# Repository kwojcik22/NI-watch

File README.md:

# NI-watch

NI-watch is an embedded watch project based on the STM32F0 MCU family. The firmware is designed for a custom hardware platform with RTC support, button input, LED feedback, alarm management, and UART-based debug logging.

## Post-production Images

  Top and bottom photos exported from the post-production media folder:

## Project Structure

A compact overview of the main repository layout:

```text
NI-watch/
├── hardware/
│   ├── doc/
│   └── zegarek/
│       ├── fp-lib-table
│       ├── jlcpcb/
│       │   └── production_files/
│       ├── Library.pretty/
│       ├── MCU.kicad_sch
│       ├── NIXIE.kicad_sch
│       ├── PWR_MNG.kicad_sch
│       ├── zegarek.kicad_pcb
│       ├── zegarek.kicad_prl
│       ├── zegarek.kicad_pro
│       ├── zegarek.kicad_sch
├── README.md
└── software/
    └── TheWatch/
        ├── Core/
        │   ├── Inc/
        │   │   ├── bsp/
        │   │   ├── logger/
        │   │   └── Manager/
        │   └── Src/
        ├── Debug/
        ├── Drivers/
        ├── STM32F091RCTX_FLASH.ld
        ├── TheWatch Debug.launch
        └── TheWatch.ioc
```

The main firmware path is `software/TheWatch/Core/`, where the primary application, peripheral drivers, and helpers are located.

## Hardware Status

The `hardware/` folder contains the KiCad board project and the JLCPCB manufacturing export data for the watch design.

- `hardware/zegarek/zegarek.kicad_pcb` is the PCB layout file.
- The project includes additional schematic sheets for the MCU and power sections: `MCU.kicad_sch`, `NIXIE.kicad_sch`, and `PWR_MNG.kicad_sch`.
- `hardware/zegarek/Library.pretty/` contains custom local footprint libraries used by the design.
- `hardware/zegarek/jlcpcb/` contains fabrication outputs and assembly data exported for JLCPCB.
  - `hardware/zegarek/jlcpcb/production_files/gerber.zip` contains the generated Gerber files for board manufacturing.
  - `hardware/zegarek/jlcpcb/production_files/` contains the exported BOM and CPL files for assembly.

## MCU Peripherals

The table below lists only the MCU peripherals used by the firmware and their primary roles.

| Peripheral | Usage | Pins / Notes |
|---|---|---|
| RTC | Timekeeping, Alarm A | on-chip RTC |
| GPIO (Buttons) | User input (short/long press) | USER: `GPIOA/B` |
| LEDs | debug feedback & heartbeat | `GPIO_LED0/1/2` |
| UART | Debug logging (logger) | USART (see `usart.c`) |
| Timers | Heartbeat, alarm buzzer and non-blocking timers | TIMx (system timers) |

## Features

- 24-hour RTC operation using the on-chip RTC peripheral
- Alarm support using RTC Alarm A
- Button press detection with short press and long press events
- LED toggling for user feedback and heartbeat status
- UART logging for debug and runtime information

## User Interaction

### Buttons

- Blue button (configured on GPIOC pin 13)
  - Short press: read current RTC time and print it to the logger
  - Long press: set the RTC alarm to one minute ahead of the current time and log the alarm value
- Additional buttons on GPIOA and GPIOB toggle onboard LEDs for quick manual feedback

### LEDs

- LEDs connected to `GPIO_LED0`, `GPIO_LED1`, and `GPIO_LED2` toggle when their respective buttons are pressed
- `LD2` is toggled periodically by a non-blocking timer to provide a simple heartbeat indicator

## RTC and Alarm Behavior

- RTC is initialized with default time and date values
- Alarm A is enabled at startup and can be updated by user input
- Alarm behavior and interrupt handling are logged through the UART debug logger

## Debugging and Logging

- Logging is implemented through `logger/logger.h` and `logger/logger.c`
- Log levels include `INFO`, `WARN`, `ERROR`, and `DEBUG`
- The firmware prints time reads, alarm configuration, button events, and interrupt notices

## Build Notes

- The firmware is built using STM32Cube-generated HAL code and project files
- The target MCU is an STM32F091RCTX device
- `software/TheWatch/STM32F091RCTX_FLASH.ld` contains the linker script for flash layout

## Notes

This README describes the current firmware behavior as implemented in the provided source files. The project is a work in progress and can be extended with additional watch features such as display output, time setting via buttons

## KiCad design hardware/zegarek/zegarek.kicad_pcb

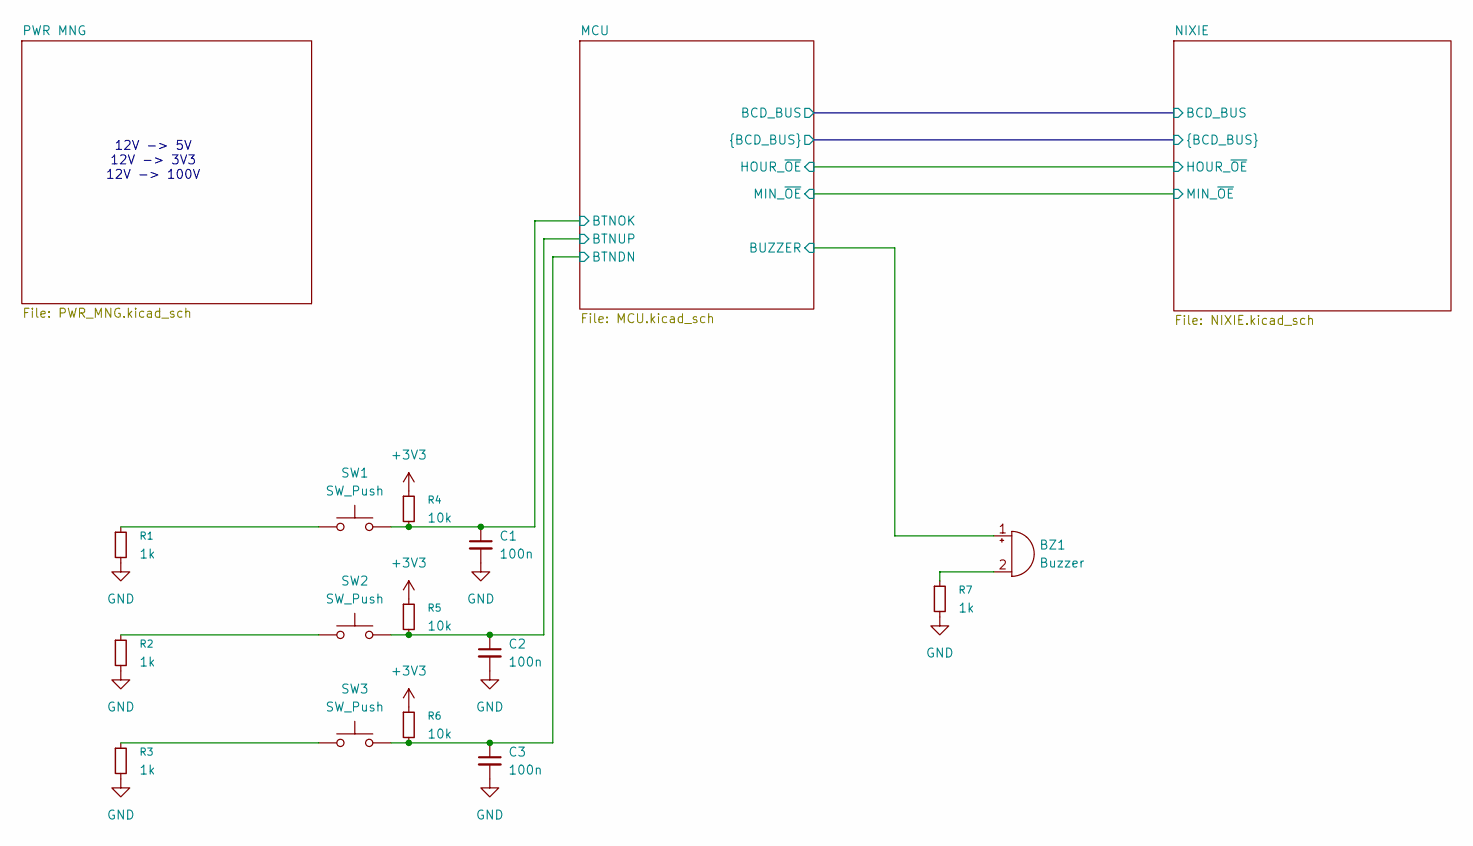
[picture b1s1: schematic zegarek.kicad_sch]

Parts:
BZ1: Buzzer; MagneticBuzzer_StarMicronics_HMB
C1, C2, C3: 100n; C_1206_3216Metric_Pad1.33x1.80mm_HandSolder; LCSC C152824
R1, R3, R7: 1k; R_0603_1608Metric_Pad0.98x0.95mm_HandSolder; LCSC C2074140
R2: 1k; R_0603_1608Metric_Pad0.98x0.95mm_HandSolder
R4, R5, R6: 10k; R_0603_1608Metric_Pad0.98x0.95mm_HandSolder; LCSC C3152147
SW1, SW2, SW3: SW_Push; SW_Push_1P1T_NO_CK_KMR2

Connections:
+3V3: R4.1, R5.1, R6.1; also elsewhere on the board
/MCU/BTNDN: C3.1, R6.2, SW3.2; also elsewhere on the board
/MCU/BTNOK: C1.1, R4.2, SW1.2; also elsewhere on the board
/MCU/BTNUP: C2.1, R5.2, SW2.2; also elsewhere on the board
/MCU/BUZZER: BZ1.1 (+); also elsewhere on the board
GND: C1.2, C2.2, C3.2, R1.2, R2.2, R3.2, R7.2; also elsewhere on the board
unnamed: BZ1.2 (-), R7.1
unnamed: R1.1, SW1.1
unnamed: R2.1, SW2.1
unnamed: R3.1, SW3.1

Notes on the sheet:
12V -> 5V 12V -> 3V3 12V -> 100V

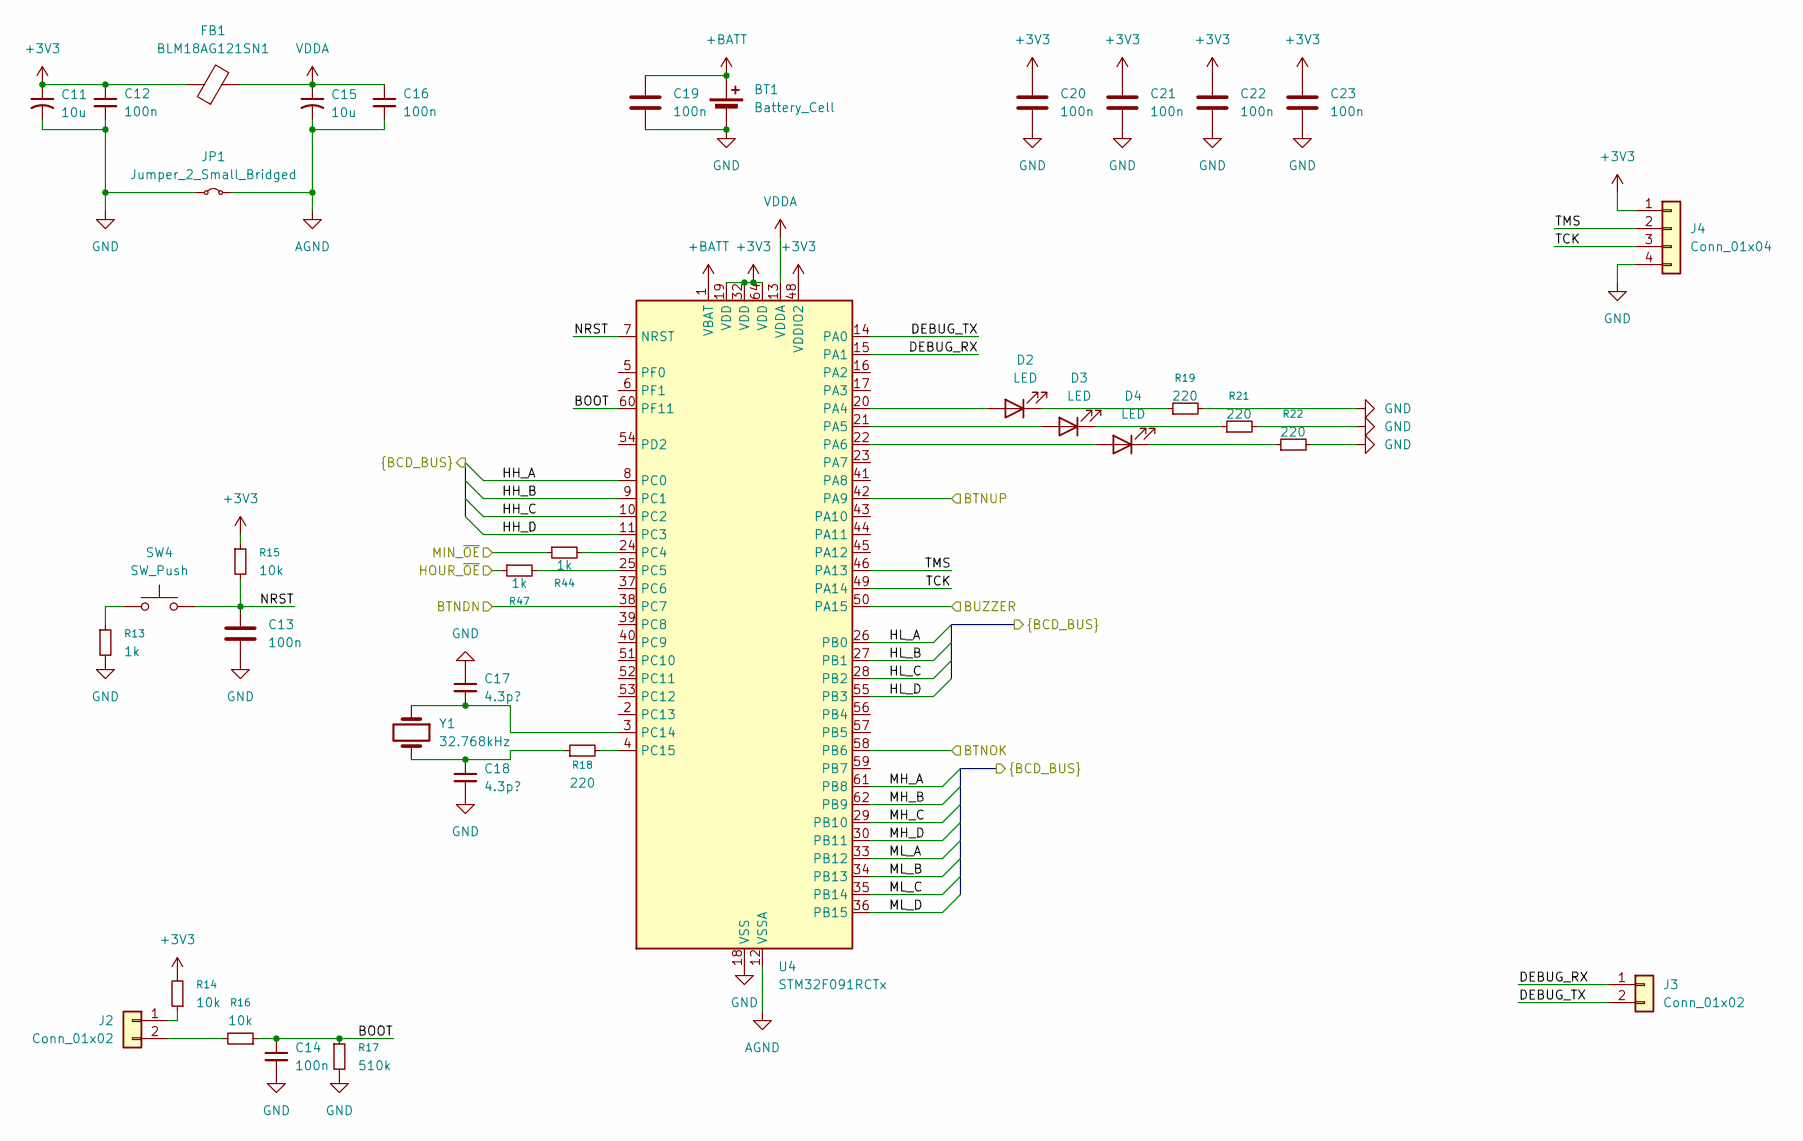
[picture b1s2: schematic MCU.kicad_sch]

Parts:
BT1: Battery_Cell; BatteryHolder_MYOUNG_BS-07-A1BJ001_CR2032; LCSC C964750
C11, C15: 10u; C_1206_3216Metric_Pad1.33x1.80mm_HandSolder; LCSC C49326738
C12, C14, C16, C19, C20, C21, C22, C23: 100n; C_1206_3216Metric_Pad1.33x1.80mm_HandSolder; LCSC C152824
C13: 100n; C_0603_1608Metric_Pad1.08x0.95mm_HandSolder; LCSC C1590
C17, C18: 4.3p?; C_0603_1608Metric_Pad1.08x0.95mm_HandSolder; LCSC C424850
D2: LED; LED_0603_1608Metric_Pad1.05x0.95mm_HandSolder; LCSC C89811
D3: LED; LED_0603_1608Metric_Pad1.05x0.95mm_HandSolder; LCSC C2286
D4: LED; LED_0603_1608Metric_Pad1.05x0.95mm_HandSolder; LCSC C2288
FB1: BLM18AG121SN1; L_0603_1608Metric_Pad1.05x0.95mm_HandSolder; LCSC C76892
J2, J3: Conn_01x02; PinHeader_1x02_P2.54mm_Vertical; LCSC C86471
J4: Conn_01x04; PinHeader_1x04_P2.54mm_Vertical; LCSC C124378
JP1: Jumper_2_Small_Bridged; SolderJumper-2_P1.3mm_Bridged_RoundedPad1.0x1.5mm
R13: 1k; R_0603_1608Metric_Pad0.98x0.95mm_HandSolder; LCSC C2074140
R14, R16: 10k; R_0603_1608Metric_Pad0.98x0.95mm_HandSolder; LCSC C15401
R15: 10k; R_0603_1608Metric_Pad0.98x0.95mm_HandSolder; LCSC C3152147
R17: 510k; R_0603_1608Metric_Pad0.98x0.95mm_HandSolder; LCSC C23192
R18, R19, R21, R22: 220; R_0603_1608Metric_Pad0.98x0.95mm_HandSolder; LCSC C54920883
R44, R47: 1k; R_0603_1608Metric_Pad0.98x0.95mm_HandSolder
SW4: SW_Push; SW_Push_1P1T_NO_CK_KMR2
U4: STM32F091RCTx; LQFP-64_10x10mm_P0.5mm; LCSC C89056
Y1: 32.768kHz; Crystal_AT310_D3.0mm_L10.0mm_Horizontal; LCSC C2236

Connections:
+3V3: C11.1, C12.1, C20.1, C21.1, C22.1, C23.1, FB1.1, J4.1, R14.2, R15.1, U4.19 (VDD), U4.32 (VDD), U4.48 (VDDIO2), U4.64 (VDD); also elsewhere on the board
+BATT: BT1.1 (+), C19.1, U4.1 (VBAT)
/MCU/BOOT: C14.1, R16.1, R17.1, U4.60 (PF11)
/MCU/BTNDN: U4.38 (PC7); also elsewhere on the board
/MCU/BTNOK: U4.58 (PB6); also elsewhere on the board
/MCU/BTNUP: U4.42 (PA9); also elsewhere on the board
/MCU/BUZZER: U4.50 (PA15); also elsewhere on the board
/MCU/DEBUG_RX: J3.1, U4.15 (PA1)
/MCU/DEBUG_TX: J3.2, U4.14 (PA0)
/MCU/HH_A: U4.8 (PC0); also elsewhere on the board
/MCU/HH_B: U4.9 (PC1); also elsewhere on the board
/MCU/HH_C: U4.10 (PC2); also elsewhere on the board
/MCU/HH_D: U4.11 (PC3); also elsewhere on the board
/MCU/HL_A: U4.26 (PB0); also elsewhere on the board
/MCU/HL_B: U4.27 (PB1); also elsewhere on the board
/MCU/HL_C: U4.28 (PB2); also elsewhere on the board
/MCU/HL_D: U4.55 (PB3); also elsewhere on the board
/MCU/HOUR_~OE: R47.1; also elsewhere on the board
/MCU/MH_A: U4.61 (PB8); also elsewhere on the board
/MCU/MH_B: U4.62 (PB9); also elsewhere on the board
/MCU/MH_C: U4.29 (PB10); also elsewhere on the board
/MCU/MH_D: U4.30 (PB11); also elsewhere on the board
/MCU/MIN_~OE: R44.1; also elsewhere on the board
/MCU/ML_A: U4.33 (PB12); also elsewhere on the board
/MCU/ML_B: U4.34 (PB13); also elsewhere on the board
/MCU/ML_C: U4.35 (PB14); also elsewhere on the board
/MCU/ML_D: U4.36 (PB15); also elsewhere on the board
/MCU/NRST: C13.1, R15.2, SW4.2, U4.7 (NRST)
/MCU/TCK: J4.3, U4.49 (PA14)
/MCU/TMS: J4.2, U4.46 (PA13)
AGND: C15.2, C16.2, JP1.2 (B), U4.12 (VSSA)
GND: BT1.2 (-), C11.2, C12.2, C13.2, C14.2, C17.1, C18.2, C19.2, C20.2, C21.2, C22.2, C23.2, J4.4, JP1.1 (A), R13.2, R17.2, R19.2, R21.2, R22.2, U4.18 (VSS), U4.31 (VSS), U4.47 (VSS), U4.63 (VSS); also elsewhere on the board
unnamed: C18.1, R18.1, Y1.2
unnamed: D2.2 (A), U4.20 (PA4)
unnamed: D2.1 (K), R19.1
unnamed: D3.2 (A), U4.21 (PA5)
unnamed: D3.1 (K), R21.1
unnamed: D4.2 (A), U4.22 (PA6)
unnamed: D4.1 (K), R22.1
unnamed: J2.1, R14.1
unnamed: J2.2, R16.2
unnamed: R13.1, SW4.1
unnamed: R44.2, U4.24 (PC4)
unnamed: R47.2, U4.25 (PC5)
unnamed: C17.2, U4.3 (PC14), Y1.1
unnamed: R18.2, U4.4 (PC15)
VDDA: C15.1, C16.1, FB1.2, U4.13 (VDDA)

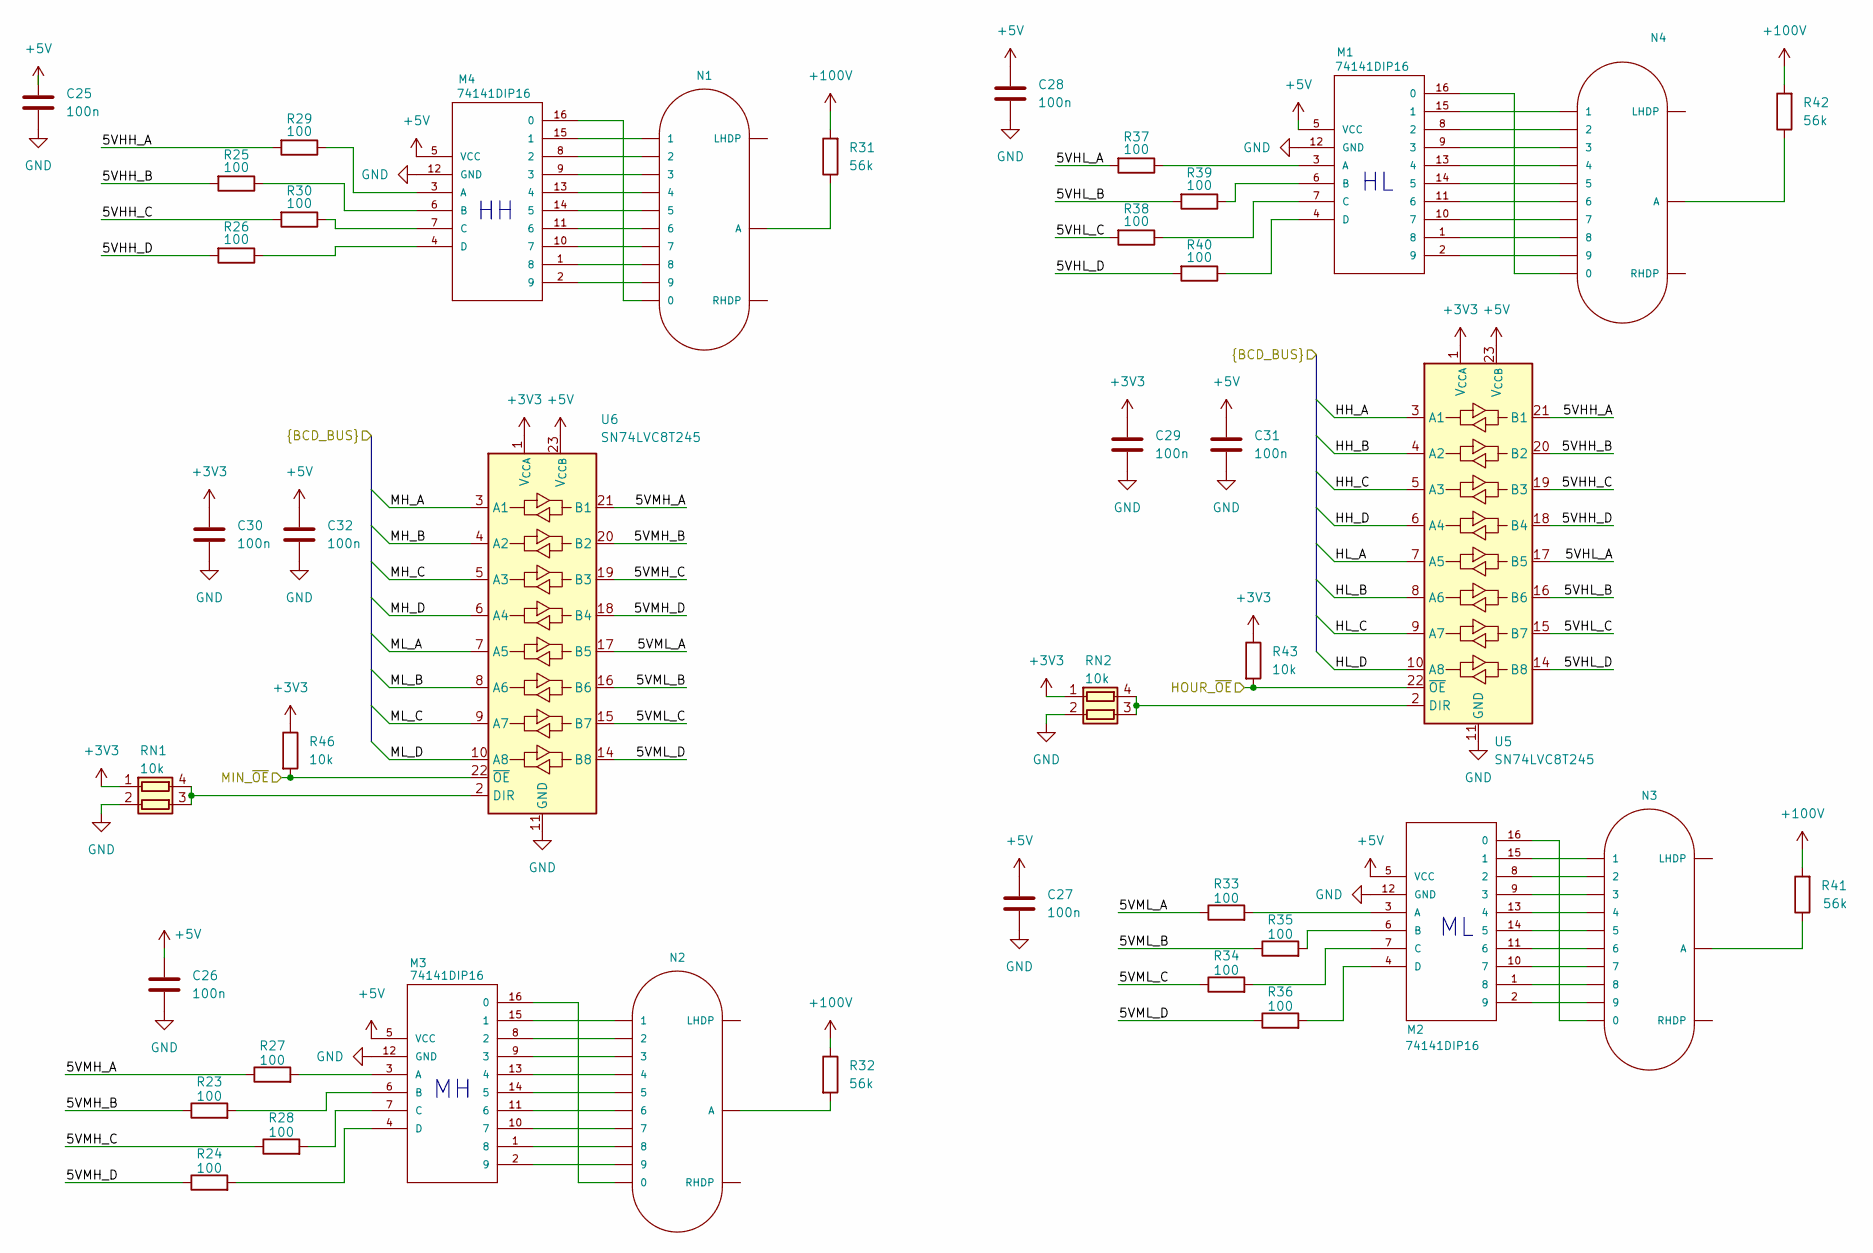
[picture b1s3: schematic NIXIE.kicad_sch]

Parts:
C25, C26, C27, C28, C29, C30, C31, C32: 100n; C_1206_3216Metric_Pad1.33x1.80mm_HandSolder; LCSC C152824
M1, M2, M3, M4: 74141DIP16; nixiemisc-DIP16
N1, N2, N3, N4: IN-14; nixies-us-IN-14
R23, R24, R25, R26, R27, R28, R29, R30, R33, R34, R35, R36, R37, R38, R39: 100; R_0603_1608Metric_Pad0.98x0.95mm_HandSolder; LCSC C3152153
R31, R32, R41, R42: 56k; R_1206_3216Metric_Pad1.30x1.75mm_HandSolder; LCSC C22809
R40: 100; R_0603_1608Metric_Pad0.98x0.95mm_HandSolder; LCSC C17901
R43, R46: 10k; R_0603_1608Metric_Pad0.98x0.95mm_HandSolder
RN1, RN2: 10k; R_Array_Convex_2x0606
U5, U6: SN74LVC8T245; TSSOP-24_4.4x7.8mm_P0.65mm

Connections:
+3V3: C29.1, C30.1, R43.1, R46.1, RN1.1 (R1.1), RN2.1 (R1.1), U5.1 (V_{CCA}), U6.1 (V_{CCA}); also elsewhere on the board
+5V: C25.1, C26.1, C27.1, C28.1, C31.1, C32.1, M1.5 (VCC), M2.5 (VCC), M3.5 (VCC), M4.5 (VCC), U5.23 (V_{CCB}), U5.24 (V_{CCB}), U6.23 (V_{CCB}), U6.24 (V_{CCB}); also elsewhere on the board
+100V: R31.2, R32.1, R41.2, R42.2; also elsewhere on the board
/MCU/HH_A: U5.3 (A1); also elsewhere on the board
/MCU/HH_B: U5.4 (A2); also elsewhere on the board
/MCU/HH_C: U5.5 (A3); also elsewhere on the board
/MCU/HH_D: U5.6 (A4); also elsewhere on the board
/MCU/HL_A: U5.7 (A5); also elsewhere on the board
/MCU/HL_B: U5.8 (A6); also elsewhere on the board
/MCU/HL_C: U5.9 (A7); also elsewhere on the board
/MCU/HL_D: U5.10 (A8); also elsewhere on the board
/MCU/HOUR_~OE: R43.2, U5.22 (~OE); also elsewhere on the board
/MCU/MH_A: U6.3 (A1); also elsewhere on the board
/MCU/MH_B: U6.4 (A2); also elsewhere on the board
/MCU/MH_C: U6.5 (A3); also elsewhere on the board
/MCU/MH_D: U6.6 (A4); also elsewhere on the board
/MCU/MIN_~OE: R46.2, U6.22 (~OE); also elsewhere on the board
/MCU/ML_A: U6.7 (A5); also elsewhere on the board
/MCU/ML_B: U6.8 (A6); also elsewhere on the board
/MCU/ML_C: U6.9 (A7); also elsewhere on the board
/MCU/ML_D: U6.10 (A8); also elsewhere on the board
/NIXIE/5VHH_A: R29.2, U5.21 (B1)
/NIXIE/5VHH_B: R25.2, U5.20 (B2)
/NIXIE/5VHH_C: R30.2, U5.19 (B3)
/NIXIE/5VHH_D: R26.2, U5.18 (B4)
/NIXIE/5VHL_A: R37.2, U5.17 (B5)
/NIXIE/5VHL_B: R39.2, U5.16 (B6)
/NIXIE/5VHL_C: R38.2, U5.15 (B7)
/NIXIE/5VHL_D: R40.2, U5.14 (B8)
/NIXIE/5VMH_A: R27.1, U6.21 (B1)
/NIXIE/5VMH_B: R23.1, U6.20 (B2)
/NIXIE/5VMH_C: R28.1, U6.19 (B3)
/NIXIE/5VMH_D: R24.1, U6.18 (B4)
/NIXIE/5VML_A: R33.1, U6.17 (B5)
/NIXIE/5VML_B: R35.1, U6.16 (B6)
/NIXIE/5VML_C: R34.1, U6.15 (B7)
/NIXIE/5VML_D: R36.1, U6.14 (B8)
GND: C25.2, C26.2, C27.2, C28.2, C29.2, C30.2, C31.2, C32.2, M1.12 (GND), M2.12 (GND), M3.12 (GND), M4.12 (GND), RN1.2 (R2.1), RN2.2 (R2.1), U5.11 (GND), U5.12 (GND), U5.13 (GND), U6.11 (GND), U6.12 (GND), U6.13 (GND); also elsewhere on the board
unnamed: M1.16 (0), N4.0
unnamed: M1.15 (1), N4.1
unnamed: M1.8 (2), N4.2
unnamed: M1.9 (3), N4.3
unnamed: M1.13 (4), N4.4
unnamed: M1.14 (5), N4.5
unnamed: M1.11 (6), N4.6
unnamed: M1.10 (7), N4.7
unnamed: M1.1 (8), N4.8
unnamed: M1.2 (9), N4.9
unnamed: M1.3 (A), R37.1
unnamed: M1.6 (B), R39.1
unnamed: M1.7 (C), R38.1
unnamed: M1.4 (D), R40.1
unnamed: M2.16 (0), N3.0
unnamed: M2.15 (1), N3.1
unnamed: M2.8 (2), N3.2
unnamed: M2.9 (3), N3.3
unnamed: M2.13 (4), N3.4
unnamed: M2.14 (5), N3.5
unnamed: M2.11 (6), N3.6
unnamed: M2.10 (7), N3.7
unnamed: M2.1 (8), N3.8
unnamed: M2.2 (9), N3.9
unnamed: M2.3 (A), R33.2
unnamed: M2.6 (B), R35.2
unnamed: M2.7 (C), R34.2
unnamed: M2.4 (D), R36.2
unnamed: M3.16 (0), N2.0
unnamed: M3.15 (1), N2.1
unnamed: M3.8 (2), N2.2
unnamed: M3.9 (3), N2.3
unnamed: M3.13 (4), N2.4
unnamed: M3.14 (5), N2.5
unnamed: M3.11 (6), N2.6
unnamed: M3.10 (7), N2.7
unnamed: M3.1 (8), N2.8
unnamed: M3.2 (9), N2.9
unnamed: M3.3 (A), R27.2
unnamed: M3.6 (B), R23.2
unnamed: M3.7 (C), R28.2
unnamed: M3.4 (D), R24.2
unnamed: M4.16 (0), N1.0
unnamed: M4.15 (1), N1.1
unnamed: M4.8 (2), N1.2
unnamed: M4.9 (3), N1.3
unnamed: M4.13 (4), N1.4
unnamed: M4.14 (5), N1.5
unnamed: M4.11 (6), N1.6
unnamed: M4.10 (7), N1.7
unnamed: M4.1 (8), N1.8
unnamed: M4.2 (9), N1.9
unnamed: M4.3 (A), R29.1
unnamed: M4.6 (B), R25.1
unnamed: M4.7 (C), R30.1
unnamed: M4.4 (D), R26.1
unnamed: N1.A, R31.1
unnamed: N2.A, R32.2
unnamed: N3.A, R41.1
unnamed: N4.A, R42.1
unnamed: RN1.3 (R2.2), RN1.4 (R1.2), U6.2 (DIR)
unnamed: RN2.3 (R2.2), RN2.4 (R1.2), U5.2 (DIR)

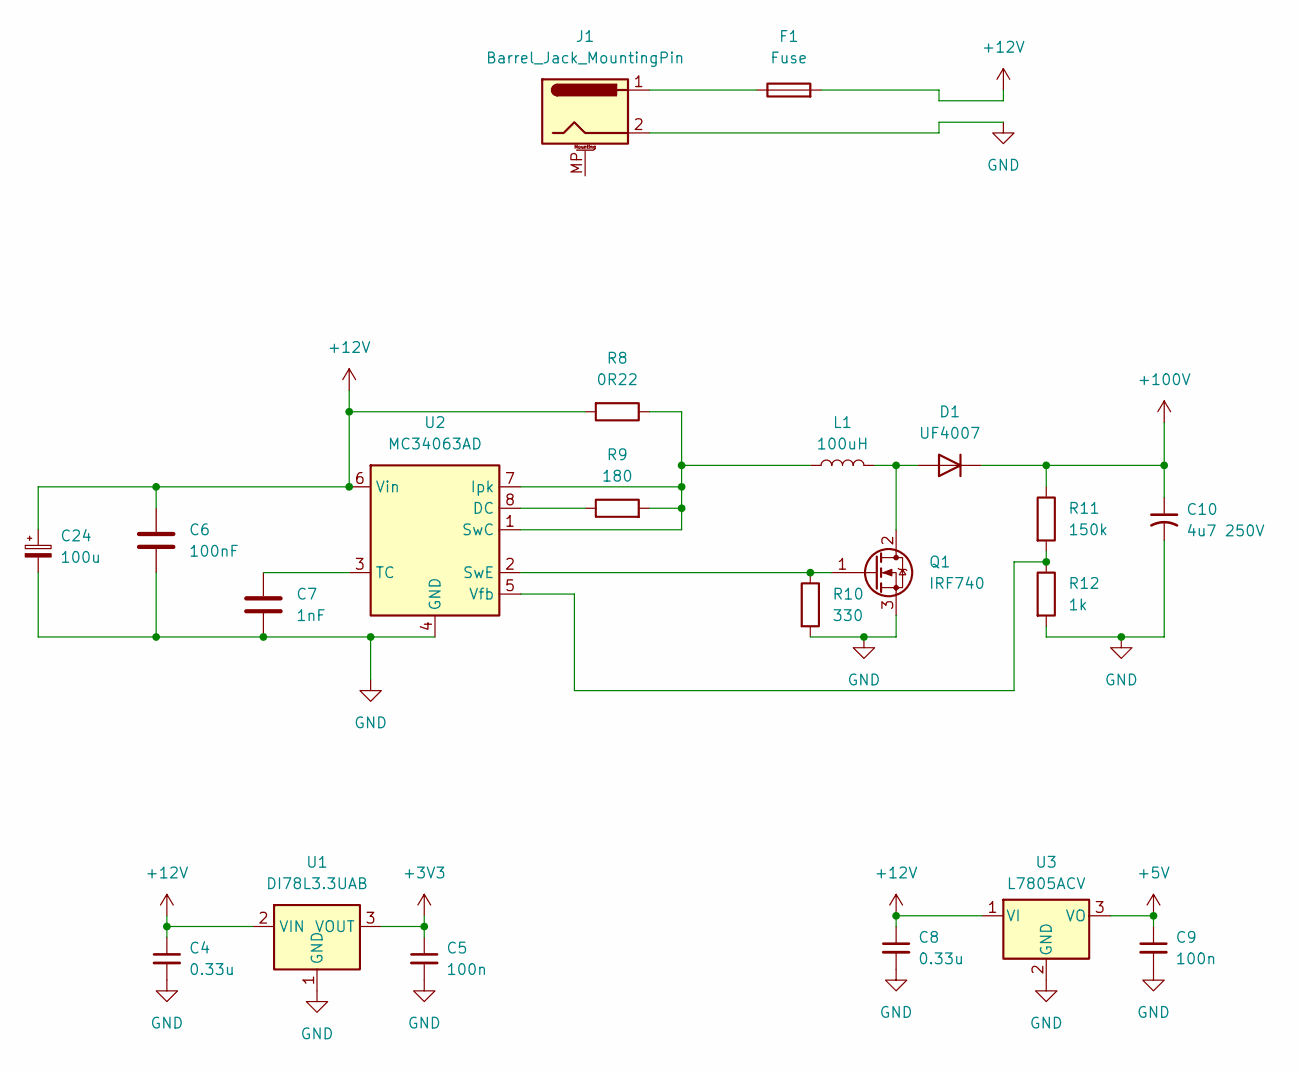
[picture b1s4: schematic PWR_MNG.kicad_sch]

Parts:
C4, C8: 0.33u; C_1206_3216Metric_Pad1.33x1.80mm_HandSolder; LCSC C274377
C5, C9: 100n; C_1206_3216Metric_Pad1.33x1.80mm_HandSolder; LCSC C152824
C6: 100nF; C_1206_3216Metric_Pad1.33x1.80mm_HandSolder; LCSC C152824
C7: 1nF; C_1206_3216Metric_Pad1.33x1.80mm_HandSolder; LCSC C49326757
C10: 4u7 250V; CP_Axial_L25.0mm_D10.0mm_P30.00mm_Horizontal
C24: 100u; C_1206_3216Metric_Pad1.33x1.80mm_HandSolder
D1: UF4007; D_DO-201AD_P15.24mm_Horizontal; LCSC C54426167
F1: Fuse; Fuse_1812_4532Metric_Pad1.30x3.40mm_HandSolder
J1: Barrel_Jack_MountingPin; BarrelJack_GCT_DCJ200-10-A_Horizontal
L1: 100uH; L_10.4x10.4_H4.8; LCSC C2045483
Q1: IRF740; TO-220-3_Horizontal_TabUp; LCSC C358408
R8: 0R22; R_1206_3216Metric_Pad1.30x1.75mm_HandSolder
R9: 180; R_1206_3216Metric_Pad1.30x1.75mm_HandSolder; LCSC C17924
R10: 330; R_0603_1608Metric_Pad0.98x0.95mm_HandSolder; LCSC C23138
R11: 150k; R_0603_1608Metric_Pad0.98x0.95mm_HandSolder; LCSC C22807
R12: 1k; R_0603_1608Metric_Pad0.98x0.95mm_HandSolder; LCSC C2074140
U1: DI78L3.3UAB; SOT-89-3
U2: MC34063AD; SOIC-8_3.9x4.9mm_P1.27mm; LCSC C2873086
U3: L7805ACV; TO-220-3_Horizontal_TabUp; LCSC C192854

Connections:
+3V3: C5.1, U1.3 (VOUT); also elsewhere on the board
+5V: C9.1, U3.3 (VO); also elsewhere on the board
+12V: C4.1, C6.2, C8.1, C24.1, F1.2, R8.2, U1.2 (VIN), U2.6 (Vin), U3.1 (VI); also elsewhere on the board
+100V: C10.1, D1.1 (K), R11.1; also elsewhere on the board
GND: C4.2, C5.2, C6.1, C7.2, C8.2, C9.2, C10.2, C24.2, J1.2, Q1.3 (S), R10.2, R12.2, U1.1 (GND), U2.4 (GND), U3.2 (GND); also elsewhere on the board
unnamed: D1.2 (A), L1.2, Q1.2 (D)
unnamed: F1.1, J1.1
unnamed: Q1.1 (G), R10.1, U2.2 (SwE)
unnamed: R9.1, U2.8 (DC)
unnamed: L1.1, R8.1, R9.2, U2.1 (SwC), U2.7 (Ipk)
unnamed: C7.1, U2.3 (TC)
unnamed: R11.2, R12.1, U2.5 (Vfb)

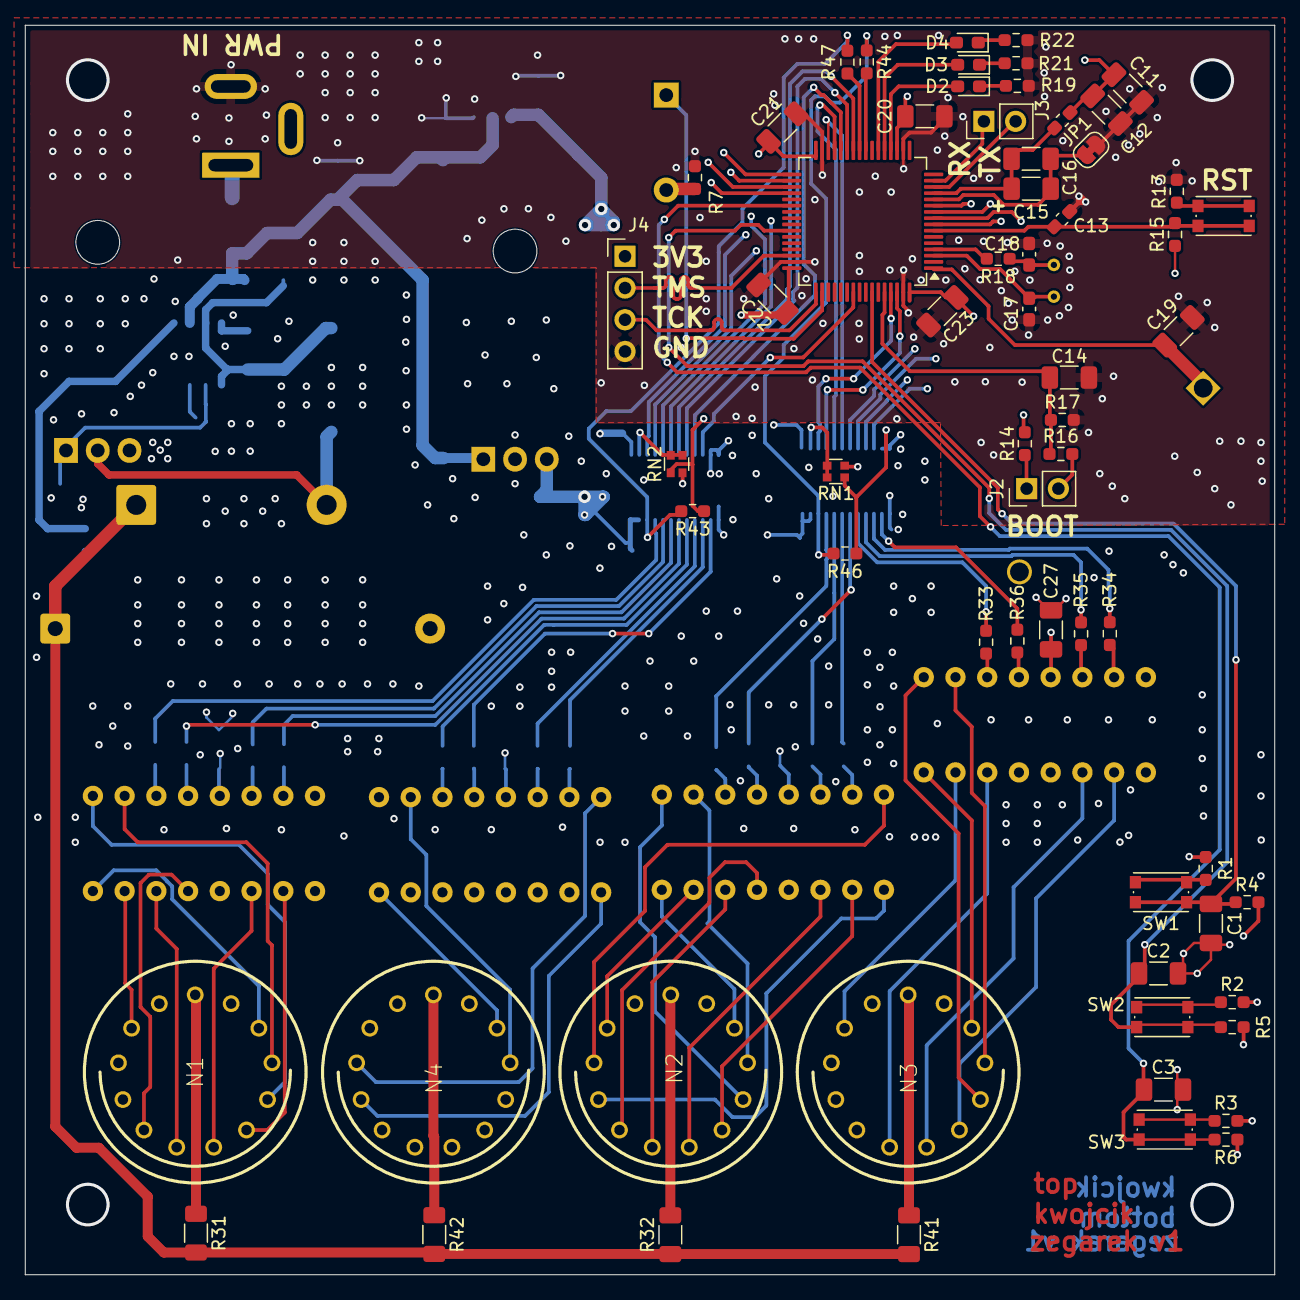
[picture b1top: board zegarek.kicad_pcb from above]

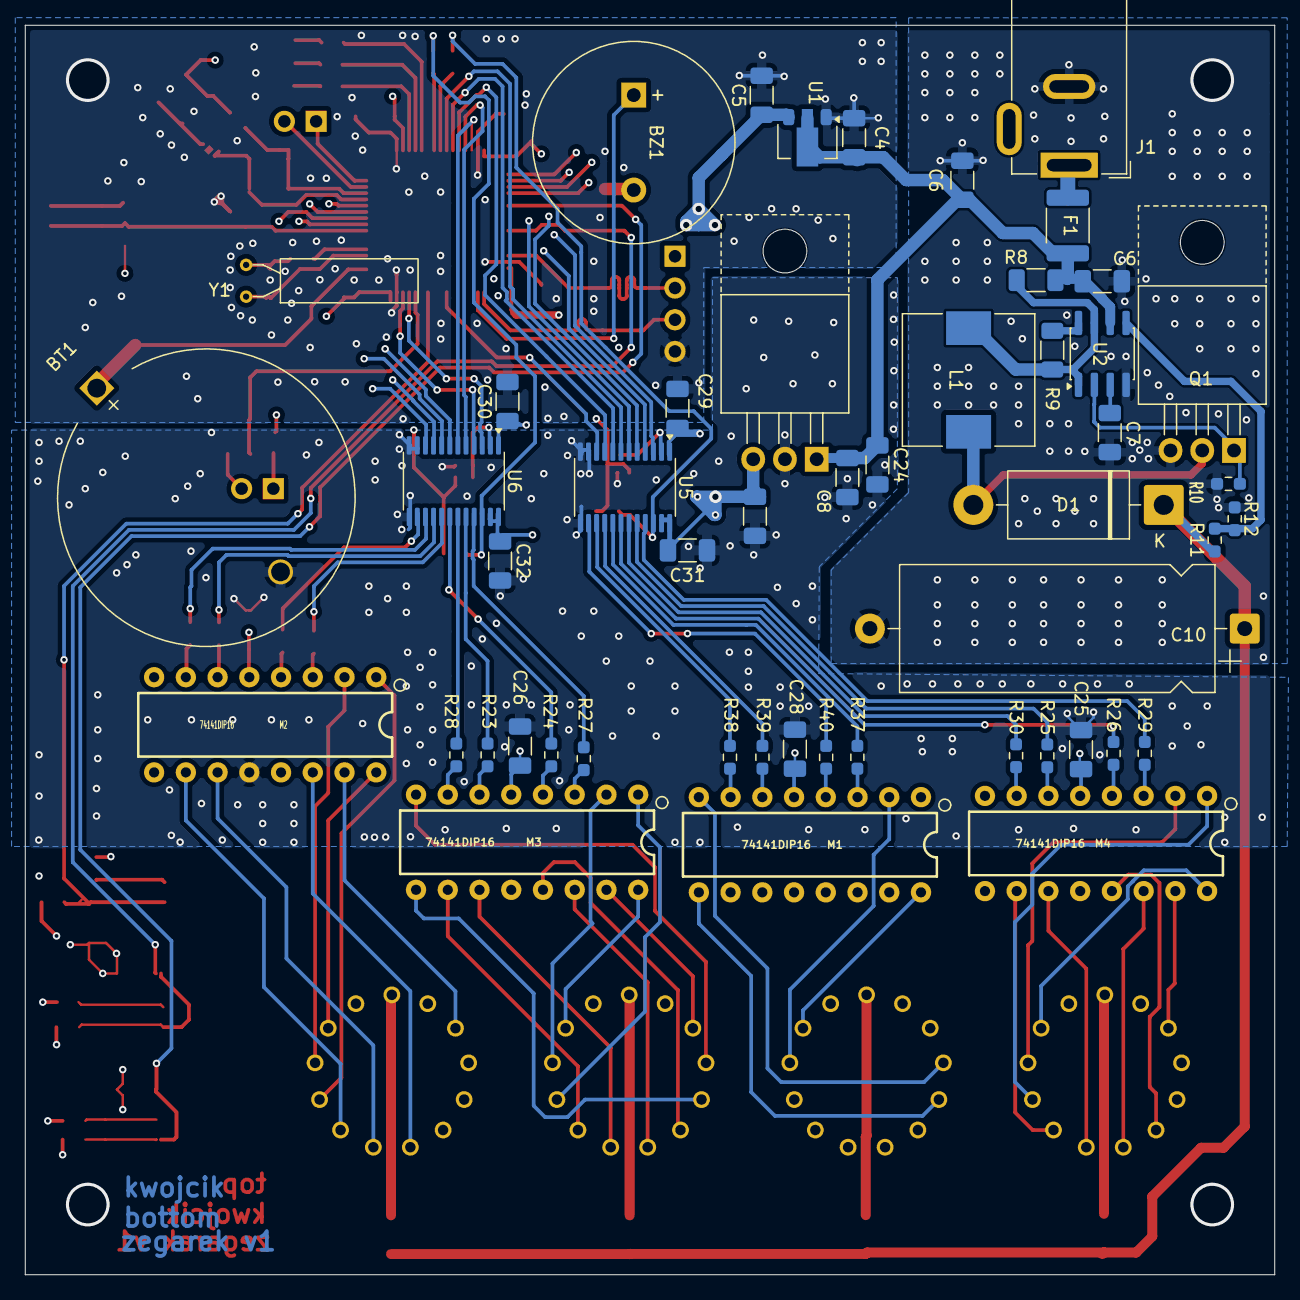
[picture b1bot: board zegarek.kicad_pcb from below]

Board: 4 copper layers, 100.0 x 100.0 mm, 114 parts (50 on the bottom side), 139 nets.

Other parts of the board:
C6#2: 100nF; C_1206_3216Metric_Pad1.33x1.80mm_HandSolder

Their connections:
+12V: C6#2.2; also elsewhere on the board
GND: C6#2.1; also elsewhere on the board

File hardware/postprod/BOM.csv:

"Reference","Qty","Value","DNP","Exclude from BOM","Exclude from Board","Footprint","Datasheet"
"BT1","1","Battery_Cell","","","","Battery:BatteryHolder_MYOUNG_BS-07-A1BJ001_CR2032",""
"BZ1","1","Buzzer","","","","Buzzer_Beeper:MagneticBuzzer_StarMicronics_HMB",""
"C1,C2,C3,C5,C9,C12,C14,C16,C19,C20,C21,C22,C23,C25,C26,C27,C28,C29,C30,C31,C32","21","100n","","","","Capacitor_SMD:C_1206_3216Metric_Pad1.33x1.80mm_HandSolder",""
"C4,C8","2","0.33u","","","","Capacitor_SMD:C_1206_3216Metric_Pad1.33x1.80mm_HandSolder",""
"C6","1","100nF","","","","Capacitor_SMD:C_1206_3216Metric_Pad1.33x1.80mm_HandSolder",""
"C7","1","1nF","","","","Capacitor_SMD:C_1206_3216Metric_Pad1.33x1.80mm_HandSolder",""
"C10","1","4u7 250V","","","","Capacitor_THT:CP_Axial_L25.0mm_D10.0mm_P30.00mm_Horizontal",""
"C11,C15","2","10u","","","","Capacitor_SMD:C_1206_3216Metric_Pad1.33x1.80mm_HandSolder",""
"C13","1","100n","","","","Capacitor_SMD:C_0603_1608Metric_Pad1.08x0.95mm_HandSolder",""
"C17,C18","2","4.3p?","","","","Capacitor_SMD:C_0603_1608Metric_Pad1.08x0.95mm_HandSolder",""
"C24","1","100u","","","","Capacitor_SMD:C_1206_3216Metric_Pad1.33x1.80mm_HandSolder",""
"D1","1","UF4007","","","","Diode_THT:D_DO-201AD_P15.24mm_Horizontal","http://www.vishay.com/docs/88756/uf5400.pdf"
"D2,D3,D4","3","LED","","","","LED_SMD:LED_0603_1608Metric_Pad1.05x0.95mm_HandSolder",""
"F1","1","Fuse","","","","Fuse:Fuse_1812_4532Metric_Pad1.30x3.40mm_HandSolder","https://www.tme.eu/pl/en/details/0zcg0150af2c/smd-polymer-fu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"
"FB1","1","BLM18AG121SN1","","","","Inductor_SMD:L_0603_1608Metric_Pad1.05x0.95mm_HandSolder","Ferryt 120Ω@100MHz, DCR~0.2Ω, w 0603"
"J1","1","Barrel_Jack_MountingPin","","","","Connector_BarrelJack:BarrelJack_GCT_DCJ200-10-A_Horizontal",""
"J2,J3","2","Conn_01x02","","","","Connector_PinHeader_2.54mm:PinHeader_1x02_P2.54mm_Vertical",""
"J4","1","Conn_01x04","","","","Connector_PinHeader_2.54mm:PinHeader_1x04_P2.54mm_Vertical",""
"JP1","1","Jumper_2_Small_Bridged","","","","Jumper:SolderJumper-2_P1.3mm_Bridged_RoundedPad1.0x1.5mm",""
"L1","1","100uH","","","","Inductor_SMD:L_10.4x10.4_H4.8",""
"M1,M2,M3,M4","4","74141DIP16","","","","nixiemisc:nixiemisc-DIP16",""
"N1,N2,N3,N4","4","IN-14","","","","nixies-us:nixies-us-IN-14",""
"Q1","1","IRF740","","","","Package_TO_SOT_THT:TO-220-3_Horizontal_TabUp","http://www.vishay.com/docs/91054/91054.pdf"
"R1,R2,R3,R7,R12,R13,R44,R47","8","1k","","","","Resistor_SMD:R_0603_1608Metric_Pad0.98x0.95mm_HandSolder",""
"R4,R5,R6,R14,R15,R16,R43,R46","8","10k","","","","Resistor_SMD:R_0603_1608Metric_Pad0.98x0.95mm_HandSolder",""
"R8","1","0R22","","","","Resistor_SMD:R_1206_3216Metric_Pad1.30x1.75mm_HandSolder",""
"R9","1","180","","","","Resistor_SMD:R_1206_3216Metric_Pad1.30x1.75mm_HandSolder",""
"R10","1","330","","","","Resistor_SMD:R_0603_1608Metric_Pad0.98x0.95mm_HandSolder",""
"R11","1","150k","","","","Resistor_SMD:R_0603_1608Metric_Pad0.98x0.95mm_HandSolder",""
"R17","1","510k","","","","Resistor_SMD:R_0603_1608Metric_Pad0.98x0.95mm_HandSolder",""
"R18,R19,R21,R22","4","220","","","","Resistor_SMD:R_0603_1608Metric_Pad0.98x0.95mm_HandSolder",""
"R23,R24,R25,R26,R27,R28,R29,R30,R33,R34,R35,R36,R37,R38,R39,R40","16","100","","","","Resistor_SMD:R_0603_1608Metric_Pad0.98x0.95mm_HandSolder",""
"R31,R32,R41,R42","4","56k","","","","Resistor_SMD:R_1206_3216Metric_Pad1.30x1.75mm_HandSolder",""
"RN1,RN2","2","10k","","","","Resistor_SMD:R_Array_Convex_2x0606",""
"SW1,SW2,SW3,SW4","4","SW_Push","","","","Button_Switch_SMD:SW_Push_1P1T_NO_CK_KMR2",""
"U1","1","DI78L3.3UAB","","","","Package_TO_SOT_SMD:SOT-89-3","https://www.holtek.com/documents/10179/116711/HT75xx-1v250.pdf"
"U2","1","MC34063AD","","","","Package_SO:SOIC-8_3.9x4.9mm_P1.27mm","http://www.onsemi.com/pub_link/Collateral/MC34063A-D.PDF"
"U3","1","L7805ACV","","","","Package_TO_SOT_THT:TO-220-3_Horizontal_TabUp","http://www.st.com/content/ccc/resource/technical/document/da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"
"U4","1","STM32F091RCTx","","","","Package_QFP:LQFP-64_10x10mm_P0.5mm","https://www.st.com/resource/en/datasheet/stm32f091rc.pdf"
"U5,U6","2","SN74LVC8T245","","","","Package_SO:TSSOP-24_4.4x7.8mm_P0.65mm","https://www.ti.com/lit/ds/symlink/sn74lvc8t245.pdf"
"Y1","1","32.768kHz","","","","Crystal:Crystal_AT310_D3.0mm_L10.0mm_Horizontal",""

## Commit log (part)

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2025-03-15 init Hw nixiepower
2025-03-15 added doc and sink in pcb
2025-03-15 links to those bought
2025-03-15 c1 pwr/gnd
2025-03-16 ordered gerber
2025-05-06 full BOM, mounted - verified footprints ok (- radiator hole)
2025-06-30 diode correction
2025-08-21 a change
2025-12-10 soft init
2026-02-05 Create TODO.md, tests modfications
2026-02-22 NIWatch soft init on vscode with LL
2026-03-16 proj struct changed to hal and loop
2026-03-16 first run at home
2026-03-25 running prototype set
2026-03-26 prototype running
